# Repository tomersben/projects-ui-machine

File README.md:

# projects-ui-machine
so this is bacicly like this mini machine with a screen buttons and a potentiometer powerd by a pi pico with a 2*10 connectoir for modules so you can connect whatever you want and then control it w[...]
it also uses a 1.69 inch color lcd screen so you cou could see the name of your action and know witch one you trigger.
to be more technical the code has an array of actions and the number you press the navigation button the arry moves one so it'll know what to trigger.

## Wiring diagram (inferred from PCB photos and code)

Below is a wiring diagram and pin mapping inferred from the PCB pictures included above and the pin assignments in the project's code (code11.ino / Program.cs). Please verify the silk / labels on your actual board before wiring — if anything doesn't match, send a clear photo of the PCB and I will update the diagram.

Signals used by the code

- SPI (display bus)
  - SCK (Clock)  -> ESP32 GPIO 18 (Configuration.SetPinFunction(18, DeviceFunction.SPI1_CLOCK))
  - MISO         -> ESP32 GPIO 19 (Configuration.SetPinFunction(19, DeviceFunction.SPI1_MISO))
  - MOSI         -> ESP32 GPIO 23 (Configuration.SetPinFunction(23, DeviceFunction.SPI1_MOSI))
  - CS (chip select) -> ESP32 GPIO 9 (SpiConnectionSettings bus 1, chip select 9)

- Display control pins
  - D/C (Data / Command) -> ESP32 GPIO 8 (_screenDc)
  - RST (Reset)          -> ESP32 GPIO 7 (_screenRst)

- Buttons
  - BTN4 -> ESP32 GPIO 14 (_btn4)
  - BTN5 -> ESP32 GPIO 15 (_btn5)

- Rotary encoder
  - ENC_SW (switch) -> ESP32 GPIO 11 (_encSw)
  - ENC_A            -> ESP32 GPIO 12 (_encA)
  - ENC_B            -> ESP32 GPIO 13 (_encB)

- Power and ground
  - 3.3V -> supply to display and logic
  - GND  -> common ground

Simple ASCII wiring sketch

Display (SPI)         ESP32 pins
┌─────────────┐        ┌────────────┐
│  Display    │        │  ESP32     │
│             │        │            │
│ MOSI <------+------- GPIO 23 (MOSI)
│ MISO <------+------- GPIO 19 (MISO)
│ SCK  <------+------- GPIO 18 (SCK)
│ CS   <------+------- GPIO 9  (CS)
│ D/C  <------+------- GPIO 8  (D/C)
│ RST  <------+------- GPIO 7  (RST)
└─────────────┘

Buttons & encoder     ESP32 pins
- BTN4  -> GPIO 14
- BTN5  -> GPIO 15
- ENC_SW -> GPIO 11
- ENC_A  -> GPIO 12
- ENC_B  -> GPIO 13

| Part                       | Price (USD) | Quantity | Link                                                                                      |
| -------------------------- | ----------: | -------: | ----------------------------------------------------------------------------------------- |
| Pi Pico                    |       $3.87 |        1 | [AliExpress](https://he.aliexpress.com/item/1005008488567735.html?utm_source=chatgpt.com) |
| Rotary Encoder             |       $2.10 |        1 | [AliExpress](https://he.aliexpress.com/item/32328753358.html?utm_source=chatgpt.com)      |
| 1.69" Screen               |       $4.51 |        1 | [AliExpress](https://he.aliexpress.com/item/1005008965476007.html?utm_source=chatgpt.com) |
| Buttons                    |       $2.60 |       50 | [AliExpress](https://he.aliexpress.com/item/1005003727160427.html?utm_source=chatgpt.com) |
| Connectors                 |       $1.54 |        1 | [AliExpress](https://he.aliexpress.com/item/1005006322027216.html?utm_source=chatgpt.com) |
| PCB Manufacturing (JLCPCB) |       $4.60 |        1 | —                                                                                         |
| 3D Printing                |           — |        1 | —                                                                                         |
| **Total**                  |  **$19.22** |          |                                                                                           |

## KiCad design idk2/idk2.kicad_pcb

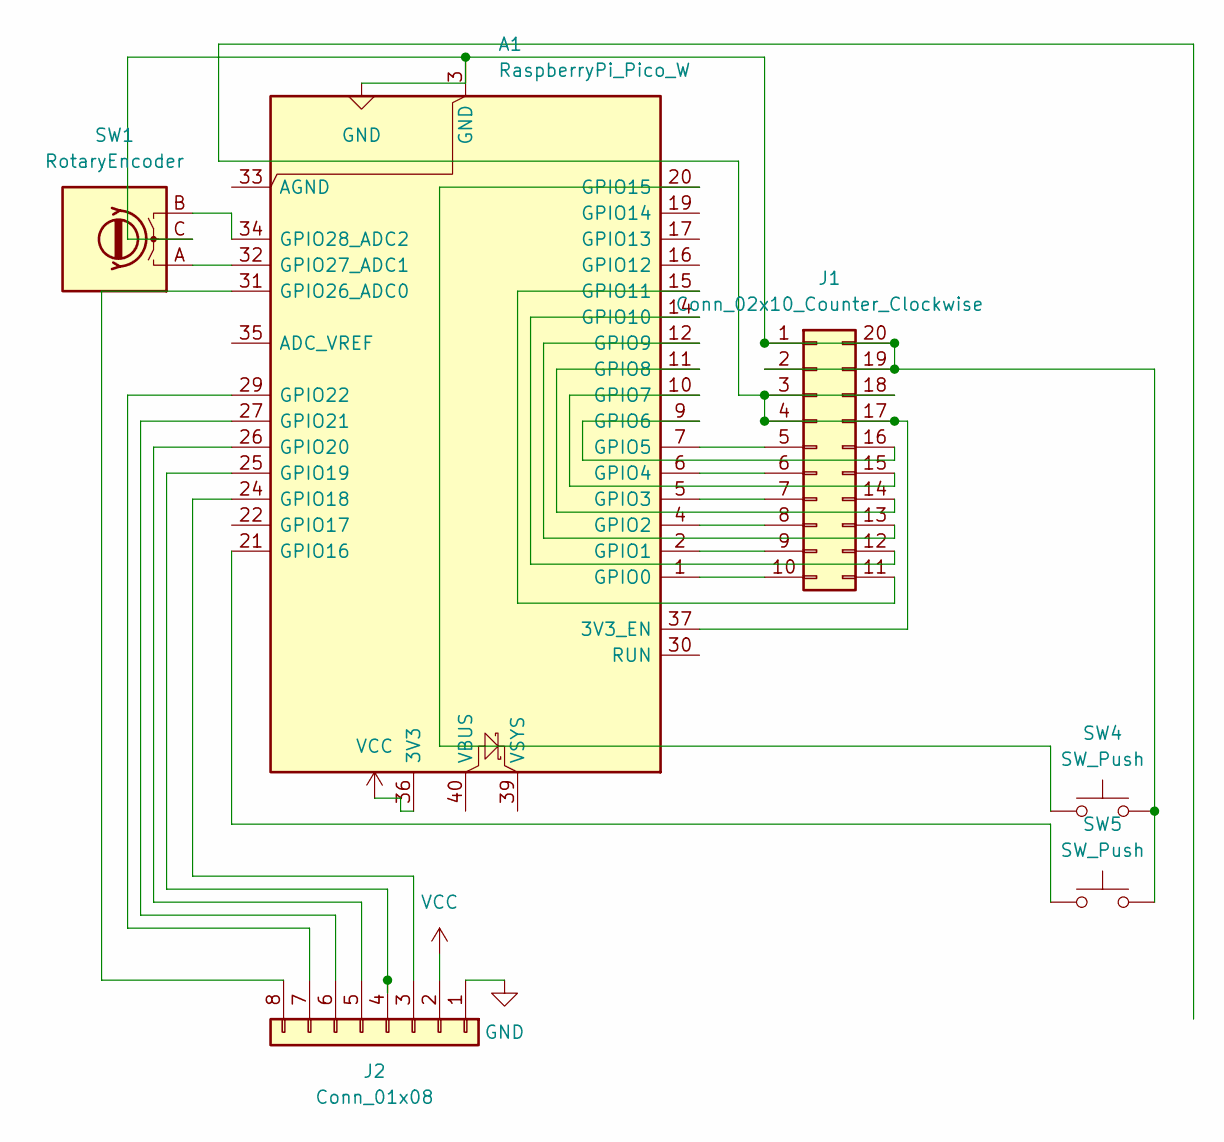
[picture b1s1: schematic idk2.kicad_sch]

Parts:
A1: RaspberryPi_Pico_W; RaspberryPi_Pico_W_SMD_HandSolder
J1: Conn_02x10_Counter_Clockwise; PinHeader_2x10_P2.54mm_Vertical
J2: Conn_01x08; PinHeader_1x08_P2.54mm_Vertical
SW1: RotaryEncoder; RotaryEncoder_Alps_EC11E_Vertical_H20mm
SW4, SW5: SW_Push; SW_PUSH_6mm

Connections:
GND: A1.3 (GND), A1.8 (GND), A1.13 (GND), A1.18 (GND), A1.23 (GND), A1.28 (GND), A1.38 (GND), J1.1, J1.2, J1.19, J1.20, J2.1, SW1.C, SW4.2, SW5.2
unnamed: A1.37 (3V3_EN), J1.3, J1.4, J1.17, J1.18
unnamed: A1.1 (GPIO0), J1.10
unnamed: A1.2 (GPIO1), J1.9
unnamed: A1.4 (GPIO2), J1.8
unnamed: A1.5 (GPIO3), J1.7
unnamed: A1.6 (GPIO4), J1.6
unnamed: A1.7 (GPIO5), J1.5
unnamed: A1.9 (GPIO6), J1.16
unnamed: A1.10 (GPIO7), J1.15
unnamed: A1.11 (GPIO8), J1.14
unnamed: A1.12 (GPIO9), J1.13
unnamed: A1.14 (GPIO10), J1.12
unnamed: A1.15 (GPIO11), J1.11
unnamed: A1.20 (GPIO15), SW4.1
unnamed: A1.21 (GPIO16), SW5.1
unnamed: A1.24 (GPIO18), J2.3
unnamed: A1.25 (GPIO19), J2.4
unnamed: A1.26 (GPIO20), J2.5
unnamed: A1.27 (GPIO21), J2.6
unnamed: A1.29 (GPIO22), J2.7
unnamed: A1.31 (GPIO26_ADC0), J2.8
unnamed: A1.32 (GPIO27_ADC1), SW1.A
unnamed: A1.34 (GPIO28_ADC2), SW1.B
VCC: A1.36 (3V3), J2.2

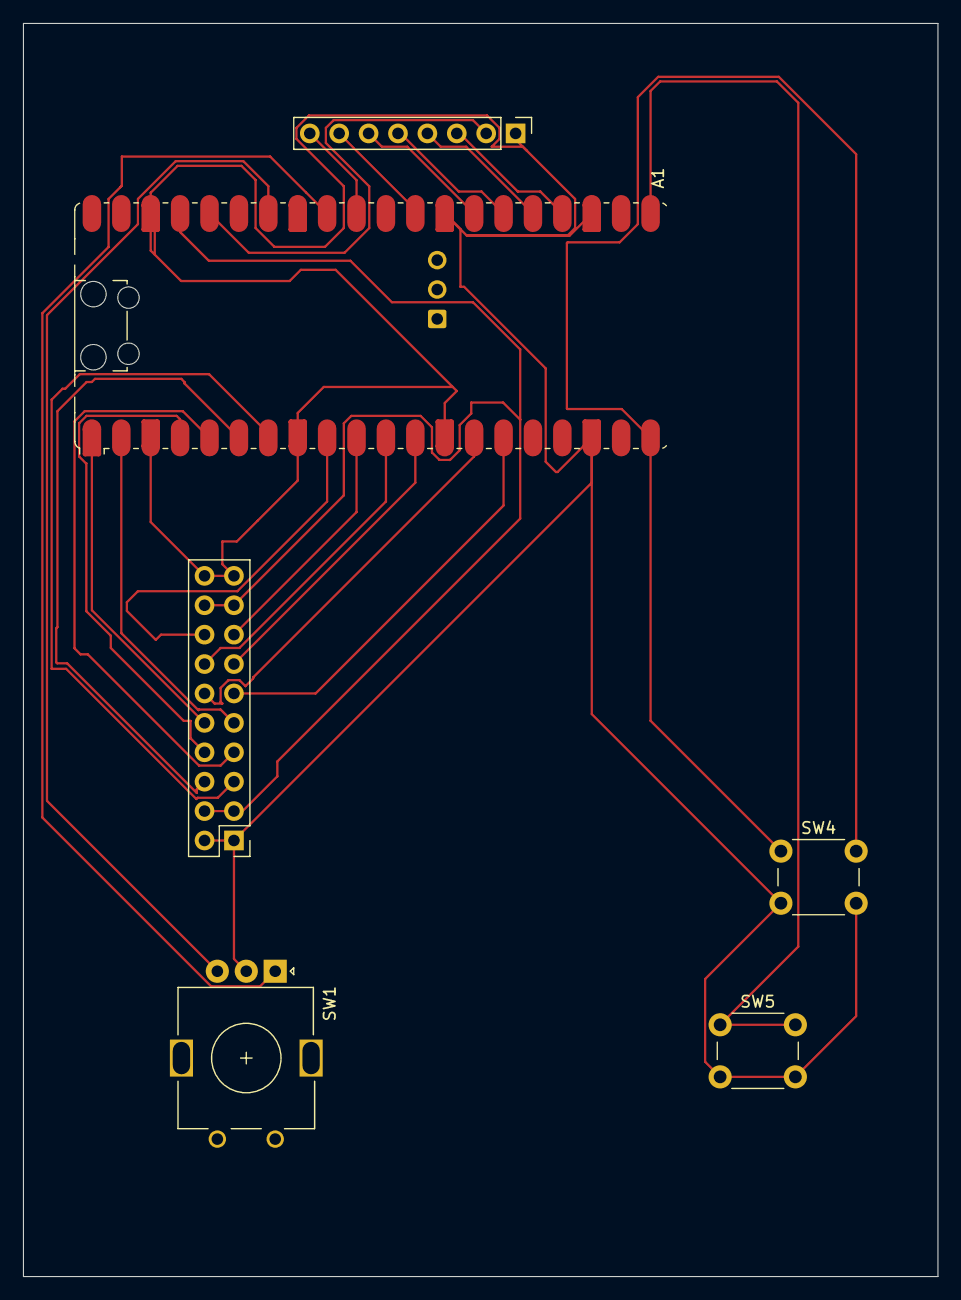
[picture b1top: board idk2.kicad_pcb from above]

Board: 2 copper layers, 79.0 x 108.2 mm, 6 parts (0 on the bottom side), 25 nets.
